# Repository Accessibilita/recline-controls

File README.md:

# Open Source Wheel Chair Recline Control System
## Hardware project for open source wheel chair recline control electronics

The Recline control system allows the wheel chair user to adjust the recline position of their chair at their leisrure. Its a complete electrical controls system with with safety in mind. The system is split across two piece of electrical hardware design as two separated printed circuit boards. The First board functions as the controller and human machine interface, the second board functions as an intelligent controller for the actuators, solenoids, and air compressor related to controlling the chair recline postion and the chair's pneumatic suspension.The human machine interface board is called the Reline Control board, and the actuator controller is called the Recline Actuator Control board. 

The system is split across two printed circuit boards for a couple of reasons, the signals from the switches and buttons are low voltage signals, running those signals through long wires would cause problems witha accurately reading the position of the rocker switches and buttons due to voltage drop, the LEDs in the 7 segment display have a low forward voltage and need to be close to the driving source for them to work, if the wire is too long voltage drop would prevent the LEDs from turning on, the other reason is the actuators and solenoids are high voltage signals and need to be mounted close to the control board. The Recline Control Board will be mounted on the arm rest of the users's dominant hand, it runs off 24V power and sends commands to the Recline Actuator control board via RS485 serial communication. The Recline Actuator Control board will be mounted in a secure location most likely at the botton of the chair between the chair and it the rolling chassis, it will be fed 24V power and connect to the Recline Control Baord via RS485. 

## Block Diagram of Entire System

# Board Specs and 3D Renders:

## Recline Control Board 

The other board, called the Recline Control board, functions as the user interface and control center. Here's what it does:

  Acts as the Human-Machine Interface (HMI): This board is where the user interacts with the system, using buttons and rocker switches to adjust the recline position of the chair.
  Processes Low-Voltage Signals: It handles low-voltage signals from the user input controls, like switches and buttons, to avoid issues with voltage drop.
  Displays Information: Includes a 7-segment display to show information, such as the recline position, which requires low forward voltage and needs to be close to the control board to avoid voltage drops.
  Sends Commands via RS485: It sends user commands to the Recline Actuator Control board through RS485 serial communication, which then controls the actuators and other high-voltage components.
  Mounted for User Access: It’s mounted on the armrest of the user's dominant hand, providing easy access for adjustments.

In essence, the Recline Control board is the user-friendly interface, interpreting user input and communicating these commands to the Recline Actuator Control board via RS485 to execute the recline and suspension adjustments.

### Specs:
- RP2040 Microcontroller
- Pololu DCDC Switching Regulator Modules for 3.3V and 5V Power
- Locking Molex connector for Rocker Switches and Buttons
- RJ45 Connector for RS485 Signals 
- Phoenix Contact high voltage connector for Power Input
- Automotive Blade Fuse Carrier and Crowbar Circuit Protection

### 3D Renders:

Top

Bottom

ISO

Side A

Side B

Side C

Side D

## Recline Actuator Control Board

The Recline Actuator Control board manages the high-voltage signals and controls the mechanical components involved in adjusting the wheelchair's recline position and pneumatic suspension. Specifically, it:

- Controls Actuators and Solenoids: It interfaces with and controls the actuators and solenoids that adjust the recline position.
- Manages the Air Compressor: It controls the air compressor for the chair's pneumatic suspension.
- Receives Commands via RS485: The board receives commands from the Recline Control board through an RS485 serial communication link.

In summary, this board serves as the power and actuator management hub, ensuring precise, responsive adjustments to the chair's recline and suspension functions based on user commands.

### Specs:
- RP2040 Microcontroller
- Pololu DCDC Switching Regulator Modules for 3.3V and 5V Power
- RJ45 Connector for RS485 Signals 
- Phoenix Contact high voltage connector for Power Input
- Automotive Blade Fuse Carrier and Crowbar Circuit Protection
- Phoenix Contact high voltage connectors for solenoids and DC Motors
- x2 VNH5019 H-Bridges
- 5 MOSFETS for controlling solenoids and air pump

### 3D Renders: 

Top

Bottom

ISO

Side A

Side B

Side C

Side D

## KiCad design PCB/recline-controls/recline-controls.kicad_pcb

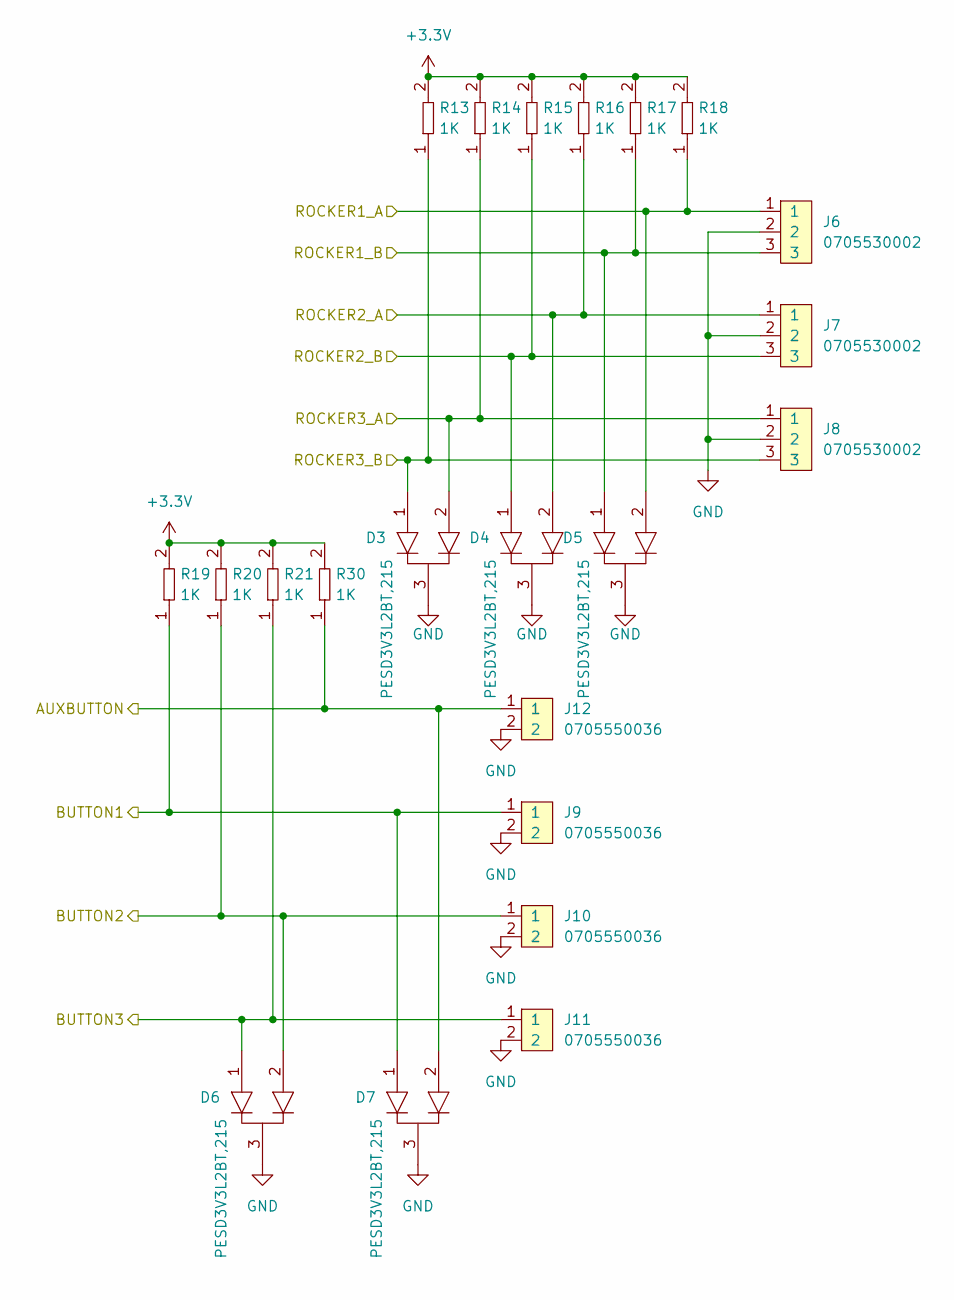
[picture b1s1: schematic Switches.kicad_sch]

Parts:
D3, D4, D5, D6, D7: PESD3V3L2BT,215; SOT-23; Tolerance *; Voltage *; MFR# PESD3V3L2BT,215
J6, J7, J8: 0705530002; Pin_Header_Angled_1x03_Pitch2.54mm; Tolerance *; Voltage *; MFR# 0705530002
J9, J10, J11, J12: 0705550036; Pin_Header_Angled_1x02_Pitch2.54mm; Tolerance *; Voltage *; MFR# 0705550036
R13, R14, R15, R16, R17, R18, R19, R20, R21, R30: RC0402FR-071KL; R0402; Tolerance 1%; Voltage *; MFR# RC0402FR-071KL

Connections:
+3.3V: R13.2, R14.2, R15.2, R16.2, R17.2, R18.2, R19.2, R20.2, R21.2, R30.2; also elsewhere on the board
/Controls and Switches/AUXBUTTON: D7.2, J12.1, R30.1; also elsewhere on the board
/Controls and Switches/BUTTON1: D7.1, J9.1, R19.1; also elsewhere on the board
/Controls and Switches/BUTTON2: D6.2, J10.1, R20.1; also elsewhere on the board
/Controls and Switches/BUTTON3: D6.1, J11.1, R21.1; also elsewhere on the board
/Controls and Switches/ROCKER1_A: D5.2, J6.1, R18.1; also elsewhere on the board
/Controls and Switches/ROCKER1_B: D5.1, J6.3, R17.1; also elsewhere on the board
/Controls and Switches/ROCKER2_A: D4.2, J7.1, R16.1; also elsewhere on the board
/Controls and Switches/ROCKER2_B: D4.1, J7.3, R15.1; also elsewhere on the board
/Controls and Switches/ROCKER3_A: D3.2, J8.1, R14.1; also elsewhere on the board
/Controls and Switches/ROCKER3_B: D3.1, J8.3, R13.1; also elsewhere on the board
GND: D3.3, D4.3, D5.3, D6.3, D7.3, J6.2, J7.2, J8.2, J9.2, J10.2, J11.2, J12.2; also elsewhere on the board

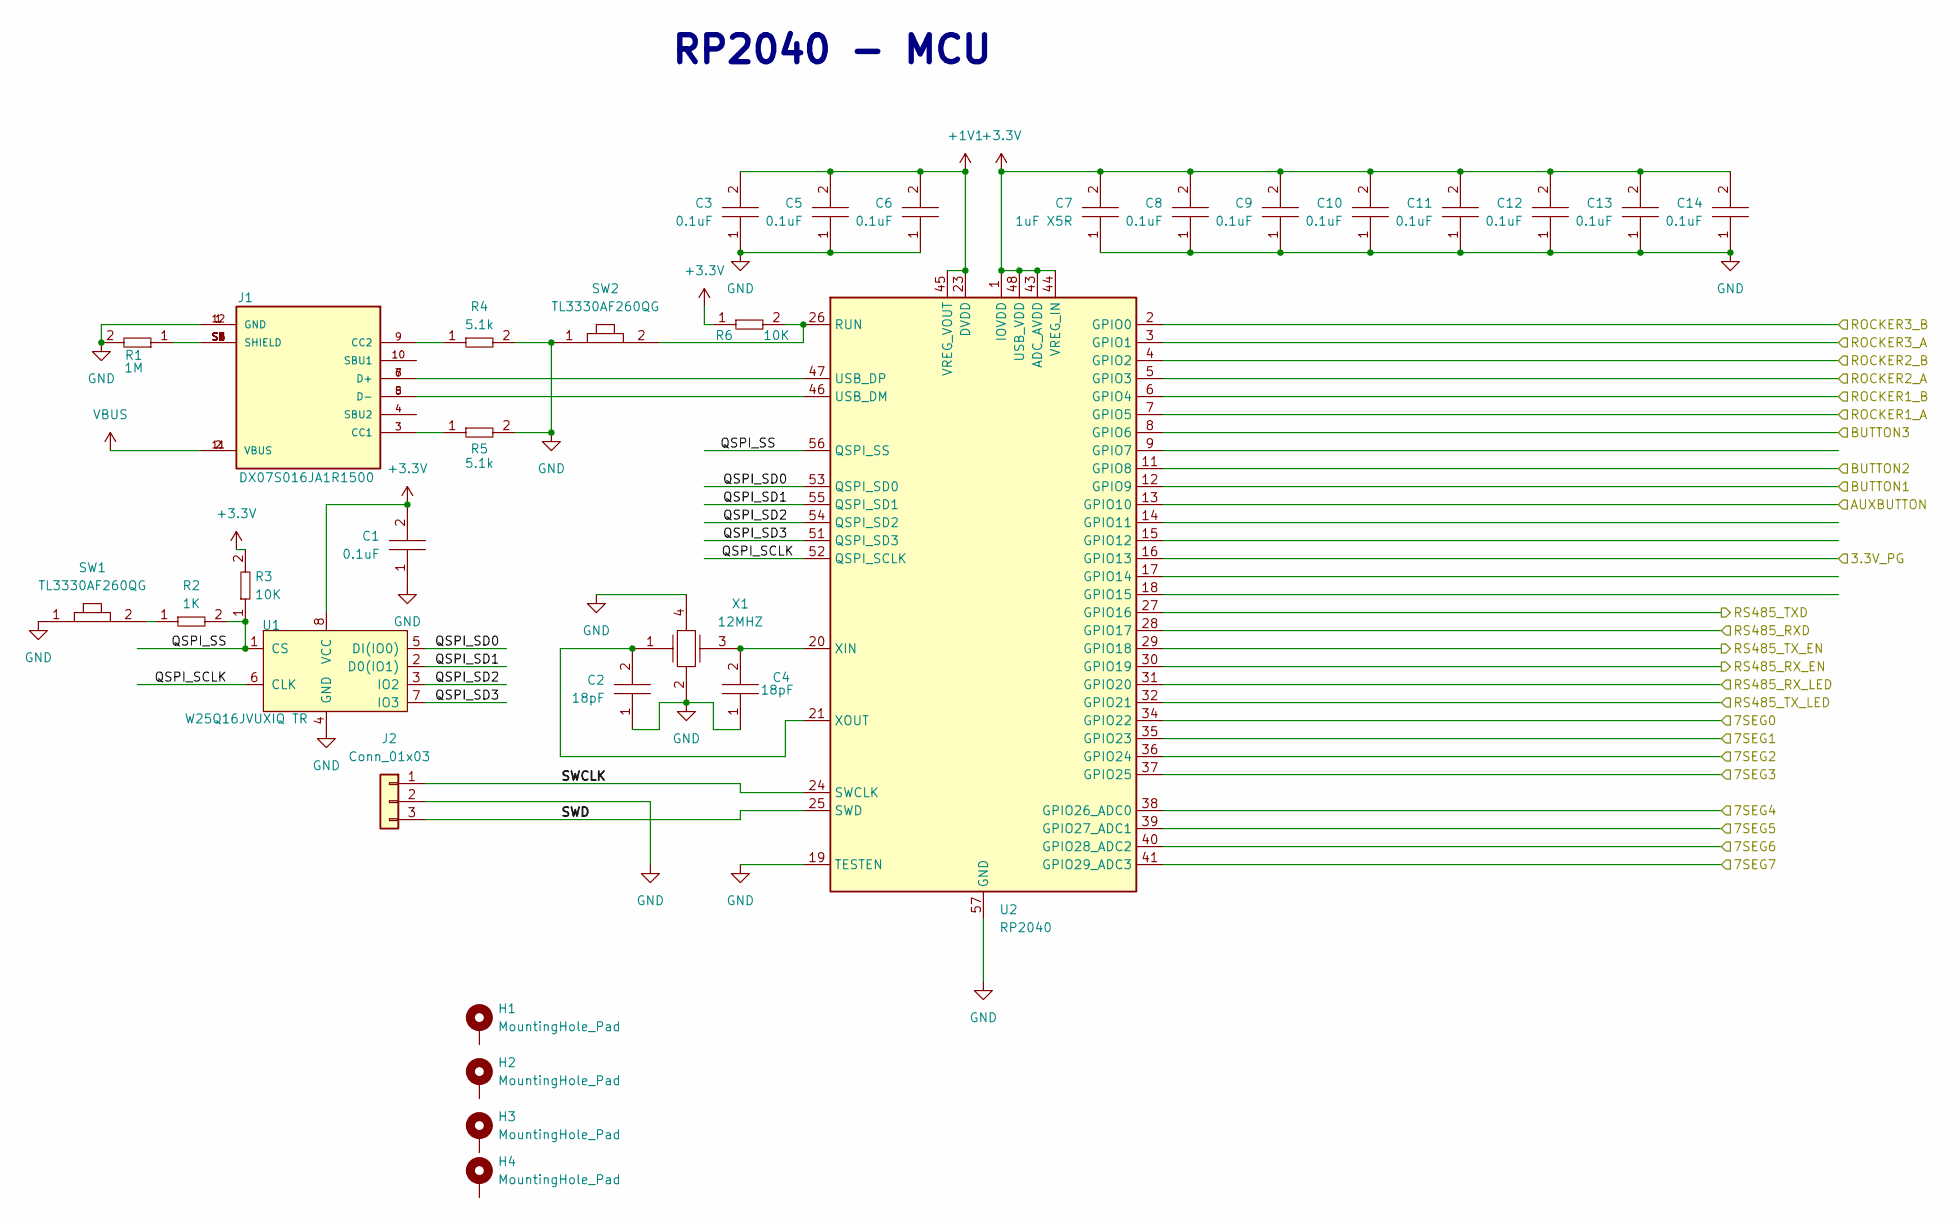
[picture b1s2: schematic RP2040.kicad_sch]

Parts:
C1, C3, C5, C6, C8, C9, C10, C11, C12, C13, C14: C0402C104K9PACTU; R0402; Tolerance 10%; Voltage 6.3V; MFR# C0402C104K9PACTU
C2, C4: GCM1555C1H180GA16D; C0402; Tolerance 2%; Voltage 50V; MFR# GCM1555C1H180GA16D
C7: CC0603KRX5R7BB105; C0603; Tolerance 10%; Voltage 16V; MFR# CC0603KRX5R7BB105
H1, H2, H3, H4: MountingHole_Pad; RPI_HAT_HOLE
J1: DX07S016JA1R1500; JAE_DX07S016JA1R1500; Tolerance *; Voltage 20V; MFR# DX07S016JA1R1500
J2: Conn_01x03; Pin_Header_Angled_1x03_Pitch2.54mm
R1: RT0603BRD071ML; R0603; Tolerance 1%; Voltage N/A; MFR# RT0603BRD071ML
R2: RC0402FR-071KL; R0402; Tolerance 1%; Voltage *; MFR# RC0402FR-071KL
R3, R6: RC0402FR-0710KL; R0402; Tolerance 1%; Voltage *; MFR# RC0402FR-0710KL
R4, R5: RC0402FR-075K1L; R0402; Tolerance 1%; Voltage N/A; MFR# RC0402FR-075K1L
SW1, SW2: TL3330AF260QG; SW_TL3330AF260QG; Tolerance *; Voltage 12VDC; MFR# TL3330AF260QG
U1: TEMPLATE; PSON50P300X200X60-9N; Tolerance *; Voltage 3.3V; MFR# W25Q16JVUXIQ TR
U2: RP2040; QFN-56-1EP_7x7mm_P0.4mm_EP3.2x3.2mm
X1: ABM8G-12.000MHZ-18-D2Y-T; XTAL_ABM8G-12.000MHZ-18-D2Y-T; Tolerance ±20ppm; Voltage *; MFR# ABM8G-12.000MHZ-18-D2Y-T

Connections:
+1V1: C3.2, C5.2, C6.2, U2.23 (DVDD), U2.45 (VREG_VOUT), U2.50 (DVDD)
+3.3V: C1.2, C7.2, C8.2, C9.2, C10.2, C11.2, C12.2, C13.2, C14.2, R3.2, R6.1, U1.8 (VCC), U2.1 (IOVDD), U2.10 (IOVDD), U2.22 (IOVDD), U2.33 (IOVDD), U2.42 (IOVDD), U2.43 (ADC_AVDD), U2.44 (VREG_IN), U2.48 (USB_VDD), U2.49 (IOVDD); also elsewhere on the board
/7 Segment Display/7SEG0: U2.34 (GPIO22); also elsewhere on the board
/7 Segment Display/7SEG1: U2.35 (GPIO23); also elsewhere on the board
/7 Segment Display/7SEG2: U2.36 (GPIO24); also elsewhere on the board
/7 Segment Display/7SEG3: U2.37 (GPIO25); also elsewhere on the board
/7 Segment Display/7SEG4: U2.38 (GPIO26_ADC0); also elsewhere on the board
/7 Segment Display/7SEG5: U2.39 (GPIO27_ADC1); also elsewhere on the board
/7 Segment Display/7SEG6: U2.40 (GPIO28_ADC2); also elsewhere on the board
/7 Segment Display/7SEG7: U2.41 (GPIO29_ADC3); also elsewhere on the board
/Controls and Switches/AUXBUTTON: U2.13 (GPIO10); also elsewhere on the board
/Controls and Switches/BUTTON1: U2.12 (GPIO9); also elsewhere on the board
/Controls and Switches/BUTTON2: U2.11 (GPIO8); also elsewhere on the board
/Controls and Switches/BUTTON3: U2.8 (GPIO6); also elsewhere on the board
/Controls and Switches/ROCKER1_A: U2.7 (GPIO5); also elsewhere on the board
/Controls and Switches/ROCKER1_B: U2.6 (GPIO4); also elsewhere on the board
/Controls and Switches/ROCKER2_A: U2.5 (GPIO3); also elsewhere on the board
/Controls and Switches/ROCKER2_B: U2.4 (GPIO2); also elsewhere on the board
/Controls and Switches/ROCKER3_A: U2.3 (GPIO1); also elsewhere on the board
/Controls and Switches/ROCKER3_B: U2.2 (GPIO0); also elsewhere on the board
/Power/3.3V_PG: U2.16 (GPIO13); also elsewhere on the board
/RP2040/QSPI_SCLK: U1.6 (CLK), U2.52 (QSPI_SCLK)
/RP2040/QSPI_SD0: U1.5 (DI(IO0)), U2.53 (QSPI_SD0)
/RP2040/QSPI_SD1: U1.2 (D0(IO1)), U2.55 (QSPI_SD1)
/RP2040/QSPI_SD2: U1.3 (IO2), U2.54 (QSPI_SD2)
/RP2040/QSPI_SD3: U1.7 (IO3), U2.51 (QSPI_SD3)
/RP2040/QSPI_SS: R2.2, R3.1, U1.1 (CS), U2.56 (QSPI_SS)
/RP2040/RS485_RXD: U2.28 (GPIO17); also elsewhere on the board
/RP2040/RS485_RX_EN: U2.30 (GPIO19); also elsewhere on the board
/RP2040/RS485_RX_LED: U2.31 (GPIO20); also elsewhere on the board
/RP2040/RS485_TXD: U2.27 (GPIO16); also elsewhere on the board
/RP2040/RS485_TX_EN: U2.29 (GPIO18); also elsewhere on the board
/RP2040/RS485_TX_LED: U2.32 (GPIO21); also elsewhere on the board
/RP2040/SWCLK: J2.1, U2.24 (SWCLK)
/RP2040/SWD: J2.3, U2.25 (SWD)
GND: C1.1, C2.1, C3.1, C4.1, C5.1, C6.1, C7.1, C8.1, C9.1, C10.1, C11.1, C12.1, C13.1, C14.1, J1.1 (GND), J1.12 (GND), J2.2, R1.2, R4.2, R5.2, SW1.1, SW2.1, U1.4 (GND), U2.19 (TESTEN), U2.57 (GND), X1.2, X1.4; also elsewhere on the board
unnamed: J1.3 (CC1), R5.1
unnamed: J1.9 (CC2), R4.1
unnamed: J1.S1 (SHIELD), J1.S2 (SHIELD), J1.S3 (SHIELD), J1.S4 (SHIELD), J1.S5 (SHIELD), J1.S6 (SHIELD), R1.1
unnamed: R2.1, SW1.2
unnamed: R6.2, SW2.2, U2.26 (RUN)
unnamed: J1.5 (D-), J1.8 (D-), U2.46 (USB_DM)
unnamed: J1.6 (D+), J1.7 (D+), U2.47 (USB_DP)
unnamed: C4.2, U2.20 (XIN), X1.3
unnamed: C2.2, U2.21 (XOUT), X1.1
VBUS: J1.2 (VBUS), J1.11 (VBUS)

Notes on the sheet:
RP2040 - MCU

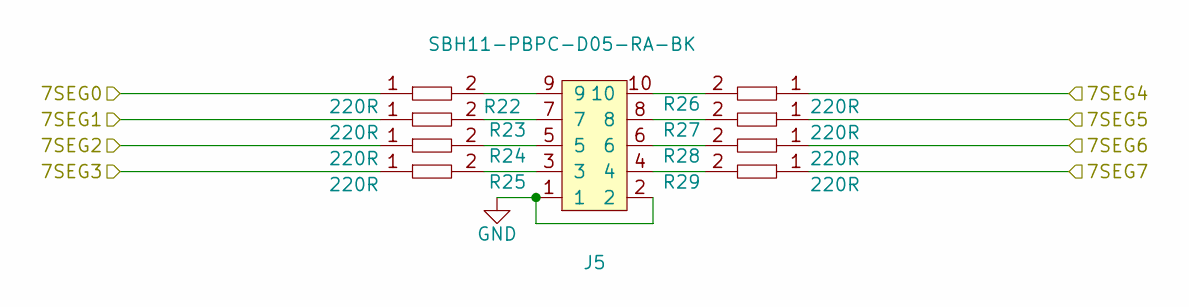
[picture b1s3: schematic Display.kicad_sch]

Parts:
J5: SBH11-PBPC-D05-RA-BK; CONN10_D05-RA-BK_SUL; Tolerance *; Voltage *; MFR# SBH11-PBPC-D05-RA-BK
R22, R23, R24, R25, R26, R27, R28, R29: RC0402FR-07220RL; R0402; Tolerance 1%; Voltage *; MFR# RC0402FR-07220RL

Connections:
/7 Segment Display/7SEG0: R22.1; also elsewhere on the board
/7 Segment Display/7SEG1: R23.1; also elsewhere on the board
/7 Segment Display/7SEG2: R24.1; also elsewhere on the board
/7 Segment Display/7SEG3: R25.1; also elsewhere on the board
/7 Segment Display/7SEG4: R26.1; also elsewhere on the board
/7 Segment Display/7SEG5: R27.1; also elsewhere on the board
/7 Segment Display/7SEG6: R28.1; also elsewhere on the board
/7 Segment Display/7SEG7: R29.1; also elsewhere on the board
GND: J5.1, J5.2; also elsewhere on the board
unnamed: J5.3, R25.2
unnamed: J5.4, R29.2
unnamed: J5.5, R24.2
unnamed: J5.6, R28.2
unnamed: J5.7, R23.2
unnamed: J5.8, R27.2
unnamed: J5.9, R22.2
unnamed: J5.10, R26.2

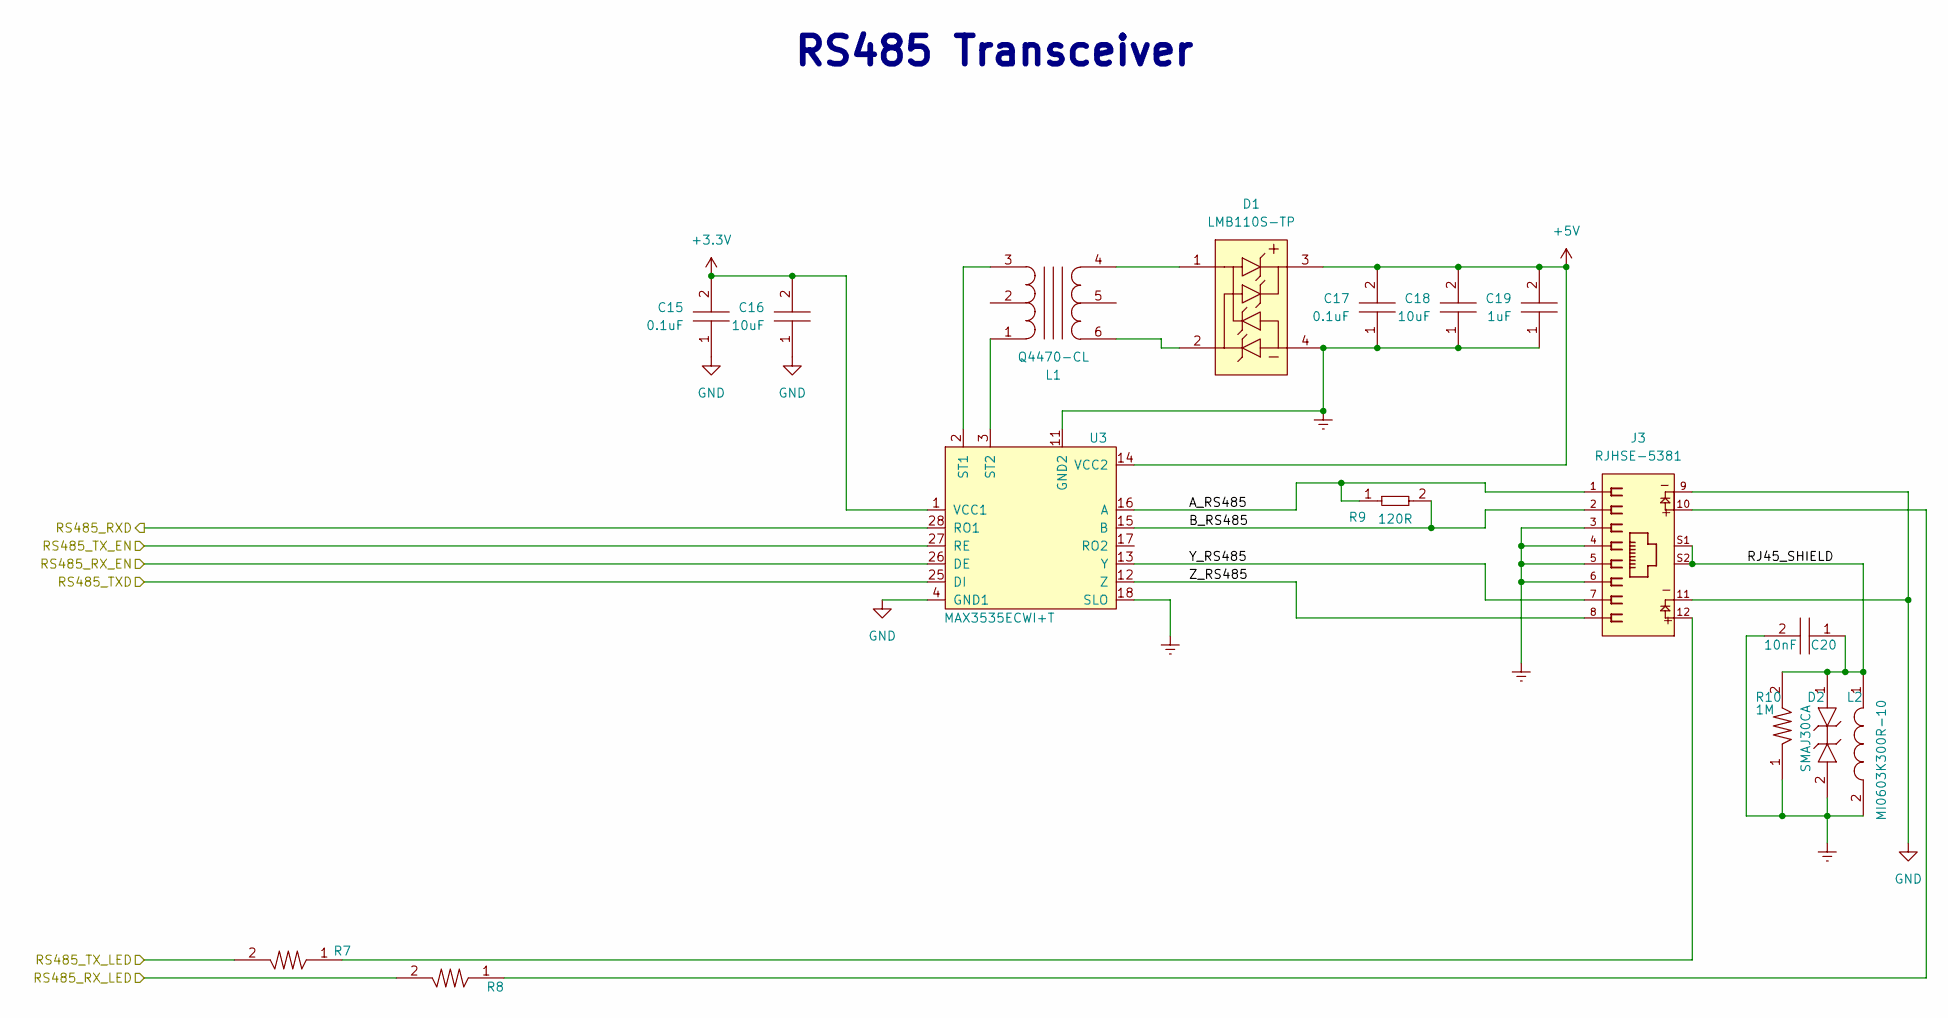
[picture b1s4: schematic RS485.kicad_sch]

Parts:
C15, C17: CL10B104JB8NNNC; C0603; Tolerance 5%; Voltage 50V; MFR# CL10B104JB8NNNC
C16, C18: CGA5L3X5R1V106K160AB; C1206; Tolerance 10%; Voltage 35V; MFR# CGA5L3X5R1V106K160AB
C19: C1206C105K3RACAUTO; D_SOD-123; Tolerance 10%; Voltage 25V; MFR# C1206C105K3RACAUTO
C20: C0805C103KCRACAUTO; C0805; Tolerance 10%; Voltage 500V; MFR# C0805C103KCRACAUTO
D1: LMB110S-TP; Tolerance *; Voltage 850 mV @ 500 mA; MFR# LMB110S-TP
D2: SMAJ30CA; Tolerance *; Voltage 30V Clamp; MFR# SMAJ30CA
J3: RJHSE-5381; AMPHENOL_RJHSE-5381; Tolerance *; Voltage *; MFR# RJHSE-5381
L1: Q4470-CL; SO6_Q4470-CL_C-SIZE_COC; Tolerance *; Voltage 5V; MFR# Q4470-CL
L2: MI0603K300R-10; Tolerance *; Voltage *; MFR# MI0603K300R-10
R7, R8: RC0603FR-07470RL; R0603; Tolerance 1%; Voltage *; MFR# RC0603FR-07470RL
R9: AC0402FR-07120RL; R0402; Tolerance 1%; Voltage *; MFR# AC0402FR-07120RL
R10: RC1206FR-071ML; R1206; Tolerance 1%; Voltage *; MFR# RC1206FR-071ML
U3: MAX3535ECWI+T; 21-0145_W28M&plus_9_MXM; Tolerance N/A; Voltage 3-5.5V; MFR# MAX3535ECWI+T

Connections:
+3.3V: C15.2, C16.2, U3.1 (VCC1); also elsewhere on the board
+5V: C17.2, C18.2, C19.2, D1.3, U3.14 (VCC2)
/RP2040/RS485_RXD: U3.26 (DE); also elsewhere on the board
/RP2040/RS485_RX_EN: U3.27 (RE); also elsewhere on the board
/RP2040/RS485_RX_LED: R7.2; also elsewhere on the board
/RP2040/RS485_TXD: U3.28 (RO1); also elsewhere on the board
/RP2040/RS485_TX_EN: U3.25 (DI); also elsewhere on the board
/RP2040/RS485_TX_LED: R8.2; also elsewhere on the board
/RS485 Transceiver/A_RS485: J3.1, R9.1, U3.16 (A)
/RS485 Transceiver/B_RS485: J3.2, R9.2, U3.15 (B)
/RS485 Transceiver/RJ45_SHIELD: C20.1, D2.1, J3.S1, J3.S2, L2.1, R10.2
/RS485 Transceiver/Y_RS485: J3.7, U3.13 (Y)
/RS485 Transceiver/Z_RS485: J3.8, U3.12 (Z)
Earth: C17.1, C18.1, C19.1, C20.2, D1.4, D2.2, J3.3, J3.4, J3.5, J3.6, L2.2, R10.1, U3.11 (GND2), U3.18 (SLO)
GND: C15.1, C16.1, J3.9, J3.11, U3.4 (GND1); also elsewhere on the board
unnamed: D1.1, L1.4
unnamed: D1.2, L1.6
unnamed: J3.10, R8.1
unnamed: J3.12, R7.1
unnamed: L1.3, U3.2 (ST1)
unnamed: L1.1, U3.3 (ST2)

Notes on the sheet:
RS485 Transceiver

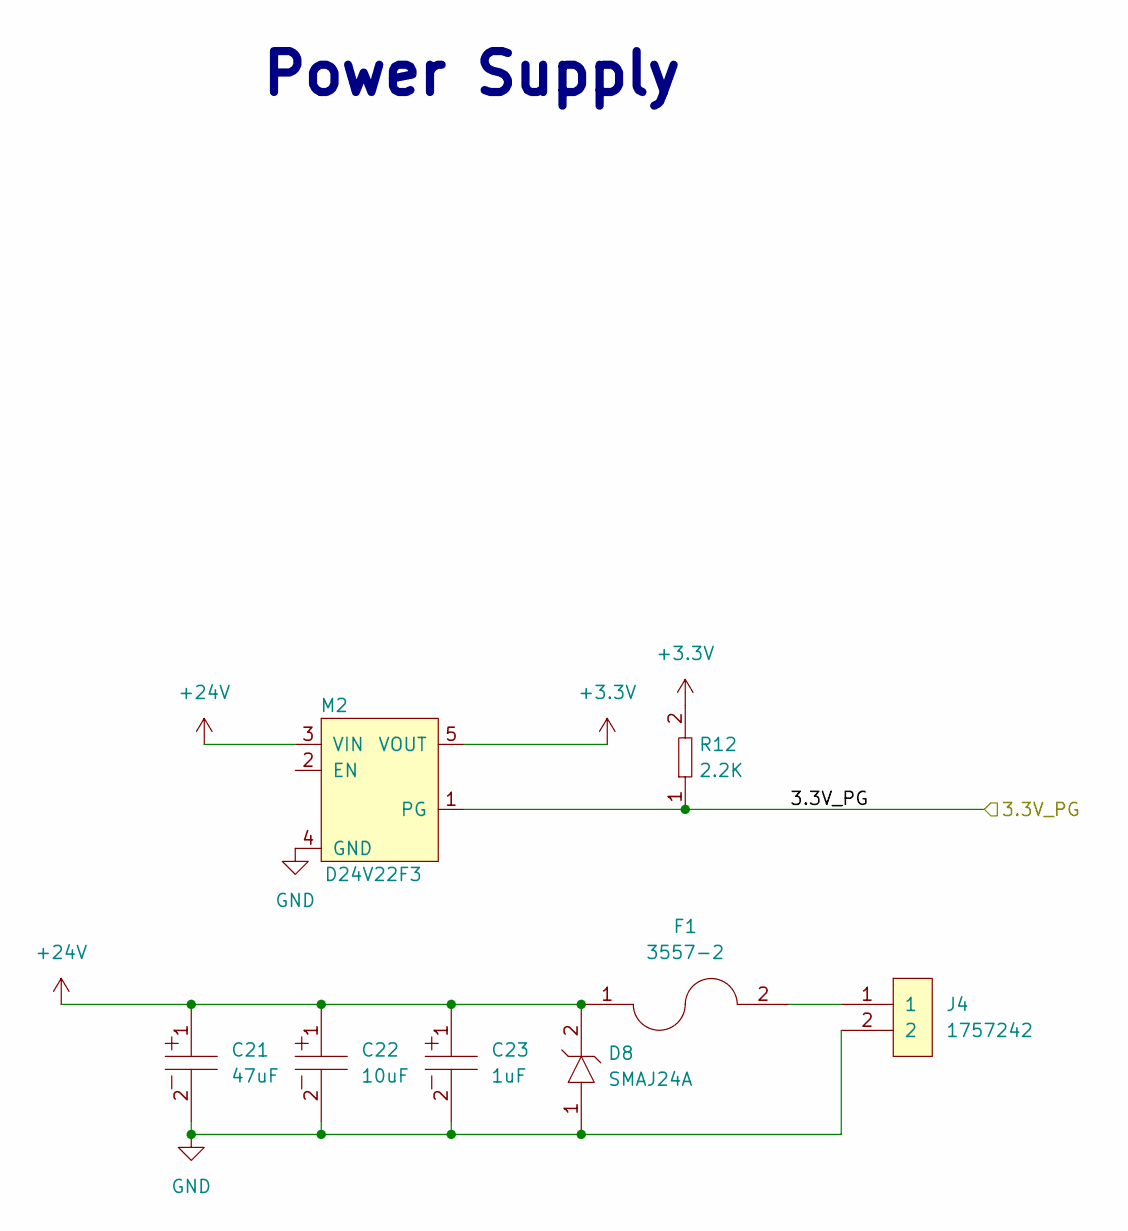
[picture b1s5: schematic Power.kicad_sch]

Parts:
C21: UUQ1H470MCL1GS; CP_Elec_8x10; Tolerance 20%; Voltage 50V; MFR# UUQ1H470MCL1GS
C22: UUQ1H100MCL1GB; CP_Elec_4x5.3; Tolerance 20%; Voltage 50V; MFR# UUQ1H100MCL1GB
C23: UUQ1H010MCL1GB; CP_Elec_4x5.3; Tolerance 20%; Voltage 50V; MFR# UUQ1H010MCL1GB
D8: SMAJ24A; SMAJ; Tolerance *; Voltage 24V RS, 26.7V VB, 38.9V Clamp; MFR# SMAJ24A
F1: 3557-2; FUSE_3557-2; Tolerance *; Voltage 500V; MFR# 3557-2
J4: 1757242; PhoenixContact_MSTBA-G_02x5.08mm_Angled; Tolerance *; Voltage 300V; MFR# 1757242
M2: D24V22F3; D24V22F12; Tolerance N/A; Voltage 36V IN 3.3V OUT; MFR# D24V22F3
R12: RC0603FR-072K2L; R0603; Tolerance 1%; Voltage N/A; MFR# RC0603FR-072K2L

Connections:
+3.3V: M2.5 (VOUT), R12.2; also elsewhere on the board
+24V: C21.1, C22.1, C23.1, D8.2, F1.1, M2.3 (VIN)
/Power/3.3V_PG: M2.1 (PG), R12.1; also elsewhere on the board
GND: C21.2, C22.2, C23.2, D8.1, J4.2, M2.4 (GND); also elsewhere on the board
unnamed: F1.2, J4.1

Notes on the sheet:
Power Supply

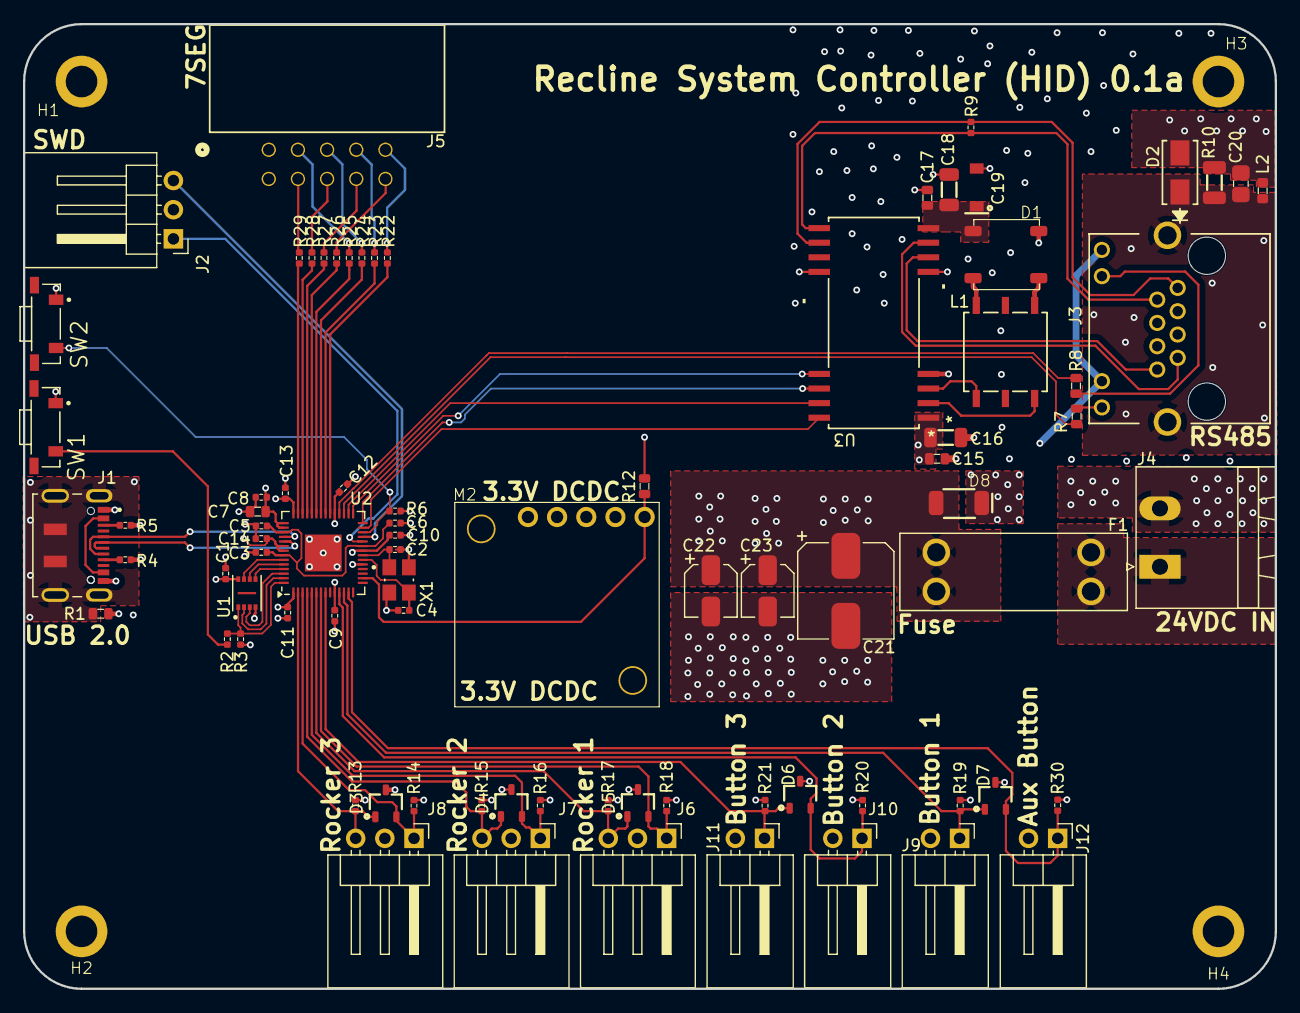
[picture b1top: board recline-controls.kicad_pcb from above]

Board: 4 copper layers, 109.0 x 84.0 mm, 86 parts (0 on the bottom side), 69 nets.

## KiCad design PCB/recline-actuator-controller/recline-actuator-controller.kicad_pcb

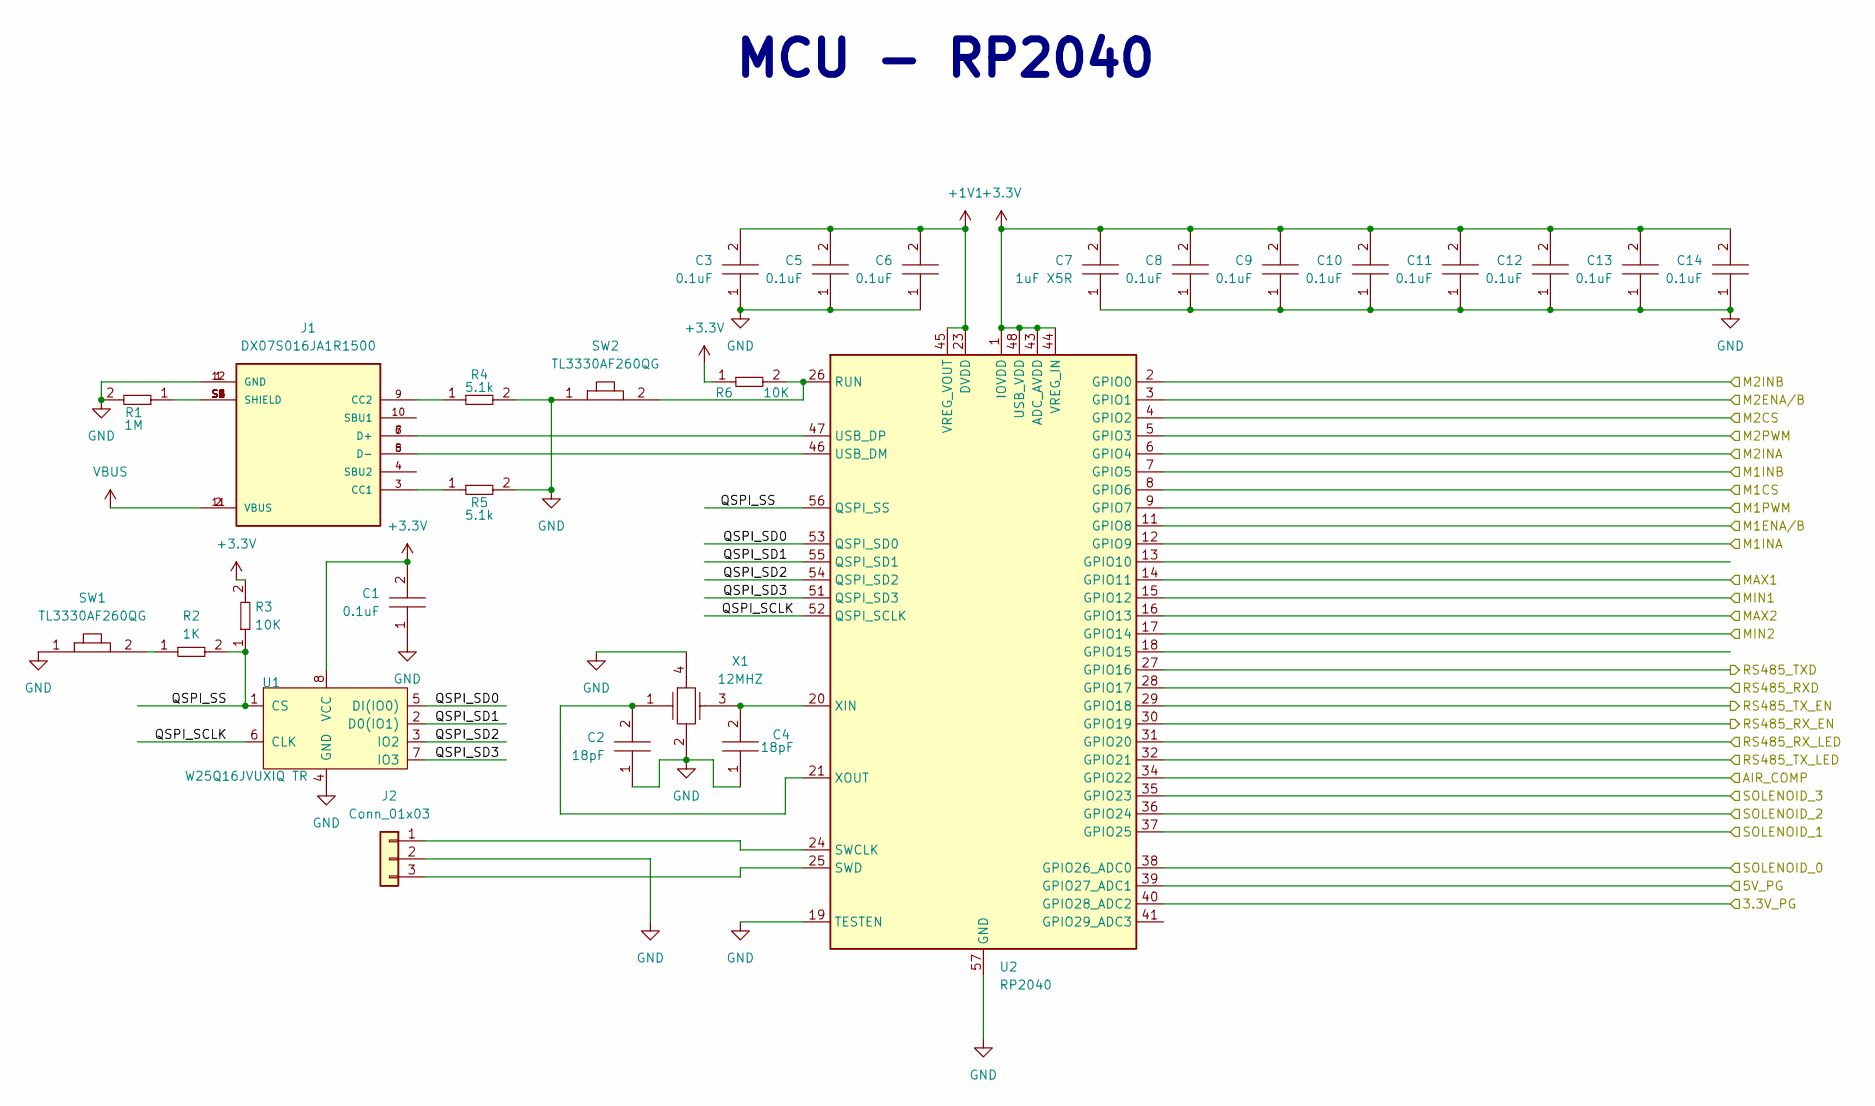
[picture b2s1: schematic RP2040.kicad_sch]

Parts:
C1, C3, C5, C6, C8, C9, C10, C11, C12, C13, C14: C0402C104K9PACTU; R0402; Tolerance 10%; Voltage 6.3V; MFR# C0402C104K9PACTU
C2, C4: GCM1555C1H180GA16D; C0402; Tolerance 2%; Voltage 50V; MFR# GCM1555C1H180GA16D
C7: CC0603KRX5R7BB105; C0603; Tolerance 10%; Voltage 16V; MFR# CC0603KRX5R7BB105
J1: DX07S016JA1R1500; JAE_DX07S016JA1R1500; Tolerance *; Voltage 20V; MFR# DX07S016JA1R1500
J2: Conn_01x03; PinHeader_1x03_P2.54mm_Vertical
R1: RT0603BRD071ML; R0603; Tolerance 1%; Voltage N/A; MFR# RT0603BRD071ML
R2: RC0402FR-071KL; R0402; Tolerance 1%; Voltage *; MFR# RC0402FR-071KL
R3, R6: RC0402FR-0710KL; R0402; Tolerance 1%; Voltage *; MFR# RC0402FR-0710KL
R4, R5: RC0402FR-075K1L; R0402; Tolerance 1%; Voltage N/A; MFR# RC0402FR-075K1L
SW1, SW2: TL3330AF260QG; SW_TL3330AF260QG; Tolerance *; Voltage 12VDC; MFR# TL3330AF260QG
U1: TEMPLATE; PSON50P300X200X60-9N; Tolerance *; Voltage 3.3V; MFR# W25Q16JVUXIQ TR
U2: RP2040; QFN-56-1EP_7x7mm_P0.4mm_EP3.2x3.2mm
X1: ABM8G-12.000MHZ-18-D2Y-T; XTAL_ABM8G-12.000MHZ-18-D2Y-T; Tolerance ±20ppm; Voltage *; MFR# ABM8G-12.000MHZ-18-D2Y-T

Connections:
+1V1: C3.2, C5.2, C6.2, U2.23 (DVDD), U2.45 (VREG_VOUT), U2.50 (DVDD)
+3.3V: C1.2, C7.2, C8.2, C9.2, C10.2, C11.2, C12.2, C13.2, C14.2, R3.2, R6.1, U1.8 (VCC), U2.1 (IOVDD), U2.10 (IOVDD), U2.22 (IOVDD), U2.33 (IOVDD), U2.42 (IOVDD), U2.43 (ADC_AVDD), U2.44 (VREG_IN), U2.48 (USB_VDD), U2.49 (IOVDD); also elsewhere on the board
/Leg Lift Motors/M3CS: U2.40 (GPIO28_ADC2); also elsewhere on the board
/Leg Lift Motors/M3ENA/B: U2.7 (GPIO5); also elsewhere on the board
/Leg Lift Motors/M3INA: U2.9 (GPIO7); also elsewhere on the board
/Leg Lift Motors/M3INB: U2.6 (GPIO4); also elsewhere on the board
/Leg Lift Motors/M3PWM: U2.8 (GPIO6); also elsewhere on the board
/Leg Lift Motors/M4CS: U2.41 (GPIO29_ADC3); also elsewhere on the board
/Leg Lift Motors/M4ENA/B: U2.4 (GPIO2); also elsewhere on the board
/Leg Lift Motors/M4INA: U2.5 (GPIO3); also elsewhere on the board
/Leg Lift Motors/M4INB: U2.2 (GPIO0); also elsewhere on the board
/Leg Lift Motors/M4PWM: U2.3 (GPIO1); also elsewhere on the board
/Motor H-Bridges/M1CS: U2.38 (GPIO26_ADC0); also elsewhere on the board
/Motor H-Bridges/M1ENA/B: U2.17 (GPIO14); also elsewhere on the board
/Motor H-Bridges/M1INA: U2.18 (GPIO15); also elsewhere on the board
/Motor H-Bridges/M1INB: U2.15 (GPIO12); also elsewhere on the board
/Motor H-Bridges/M1PWM: U2.16 (GPIO13); also elsewhere on the board
/Motor H-Bridges/M2CS: U2.39 (GPIO27_ADC1); also elsewhere on the board
/Motor H-Bridges/M2ENA/B: U2.12 (GPIO9); also elsewhere on the board
/Motor H-Bridges/M2INA: U2.14 (GPIO11); also elsewhere on the board
/Motor H-Bridges/M2INB: U2.11 (GPIO8); also elsewhere on the board
/Motor H-Bridges/M2PWM: U2.13 (GPIO10); also elsewhere on the board
/RP2040/QSPI_SCLK: U1.6 (CLK), U2.52 (QSPI_SCLK)
/RP2040/QSPI_SD0: U1.5 (DI(IO0)), U2.53 (QSPI_SD0)
/RP2040/QSPI_SD1: U1.2 (D0(IO1)), U2.55 (QSPI_SD1)
/RP2040/QSPI_SD2: U1.3 (IO2), U2.54 (QSPI_SD2)
/RP2040/QSPI_SD3: U1.7 (IO3), U2.51 (QSPI_SD3)
/RP2040/QSPI_SS: R2.2, R3.1, U1.1 (CS), U2.56 (QSPI_SS)
/RP2040/RS485_RXD: U2.28 (GPIO17); also elsewhere on the board
/RP2040/RS485_RX_EN: U2.30 (GPIO19); also elsewhere on the board
/RP2040/RS485_RX_LED: U2.36 (GPIO24); also elsewhere on the board
/RP2040/RS485_TXD: U2.27 (GPIO16); also elsewhere on the board
/RP2040/RS485_TX_EN: U2.29 (GPIO18); also elsewhere on the board
/RP2040/RS485_TX_LED: U2.37 (GPIO25); also elsewhere on the board
/RP2040/SPI0_CSn: U2.32 (GPIO21); also elsewhere on the board
/RP2040/SPI0_RX: U2.31 (GPIO20); also elsewhere on the board
/RP2040/SPI0_SCK: U2.34 (GPIO22); also elsewhere on the board
unnamed: J1.3 (CC1), R5.1
unnamed: J1.9 (CC2), R4.1
unnamed: J1.S1 (SHIELD), J1.S2 (SHIELD), J1.S3 (SHIELD), J1.S4 (SHIELD), J1.S5 (SHIELD), J1.S6 (SHIELD), R1.1
unnamed: J2.1, U2.24 (SWCLK)
unnamed: J2.3, U2.25 (SWD)
unnamed: R2.1, SW1.2
unnamed: R6.2, SW2.2, U2.26 (RUN)
unnamed: J1.5 (D-), J1.8 (D-), U2.46 (USB_DM)
unnamed: J1.6 (D+), J1.7 (D+), U2.47 (USB_DP)
unnamed: C4.2, U2.20 (XIN), X1.3
unnamed: C2.2, U2.21 (XOUT), X1.1
VBUS: J1.2 (VBUS), J1.11 (VBUS)

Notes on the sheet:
MCU - RP2040
